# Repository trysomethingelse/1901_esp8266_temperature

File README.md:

# ESP8266_temperature
ESP8266 works as MQTT client and sends temperature to MQTT Broker. Paho client in python reads new data and saves in sql database. HTTP server with Dash reads new data when site is refreshed and shows it on graph.

## How to start?
(tested on Windows 10)
1. Flash new firmware to yours ESP (working firmware is at firmware location on GitHub)
2. Upload all files from LUA folder to your ESP and create additional file ("credentials.lua") with your wifi network infromation as given below:

`SSID = "ssid_of_your_network"`

`PASSWORD = "password_of_your_network"`
 
3. Run mosquitto broker

4. Run python script `main.py` . Script will create database file at location and name given inside script. Then received data from esp will go to database. Http server should be available at default address http://127.0.0.1:8050/

:exclamation: At first run of ESP network should be available because of time synchronization. If not esp will stuck. After first synchronization data will be saved in memory if network will be not accessible and in new connection all of it will be transmitted.

## How to change time interval of deep sleep with MQTT?

Publish to path: esp/set where message is time interval in seconds, max is about 71 min.

For example:

`mosquitto_pub -t esp/set -m 60 -h 192.168.137.1`

## Electronic schematic:

## Data presentation:

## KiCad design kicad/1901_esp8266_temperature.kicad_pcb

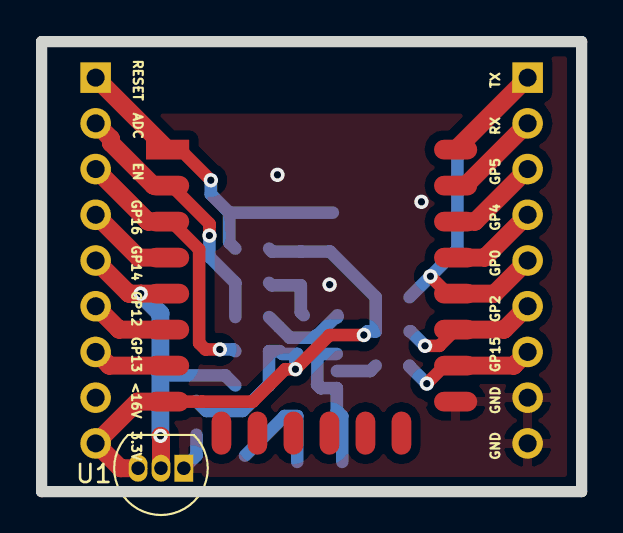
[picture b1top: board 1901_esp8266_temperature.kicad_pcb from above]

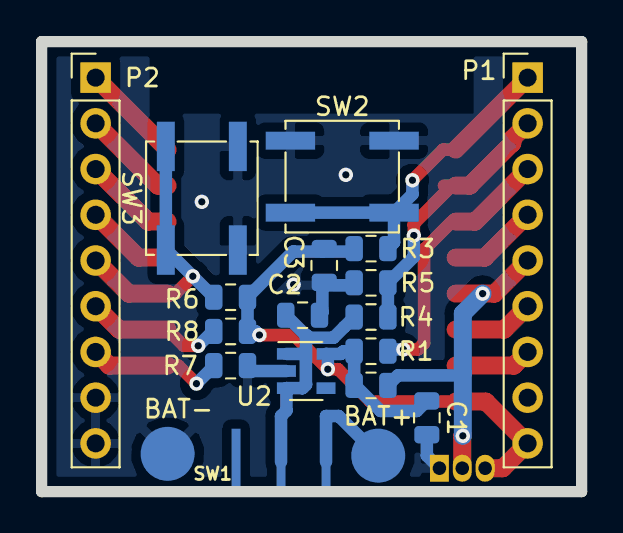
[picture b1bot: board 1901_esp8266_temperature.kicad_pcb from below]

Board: 2 copper layers, 30.0 x 25.0 mm, 21 parts (19 on the bottom side), 18 nets.

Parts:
BAT+: PAD_BAT+; Pad
BAT-: PAD_BAT-; Pad
C1: 22uF; C_0805_2012Metric
C2, C3: 1uF; C_0805_2012Metric
P1, P2: CONN_01X09; PinHeader_1x09_P2.54mm_Vertical
R1, R3, R6, R7, R8: 10KΩ; R_0805_2012Metric
R2: 4.7k; R_0805_2012Metric
R4, R5: 1MΩ; R_0805_2012Metric
SW1: pkl_SWITCH-SPDT; SW_SS12D00_SMD
SW2: SW_RESET; SW_SPST_EVPBF
SW3: SW_FLASH; SW_SPST_EVPBF
U1: DS18B20; TO-92_Inline
U2: XC6210B332MR; SOT-23-5
U3: ESP-12E

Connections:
+3V3: C1.1, C3.1, P1.9, R1.1, R2.1, R3.1, R6.1, R8.1, U1.3, U2.5, U3.8
+BATT: C2.1, R4.1, SW1.2, U2.1, U2.3
BATT_SENSE: P1.2, R4.2, R5.1, U3.2
DS_TEMP: P1.5, R2.2, U1.2, U3.5
GND: BAT-.1, C1.2, C2.2, C3.2, P2.8, P2.9, R5.2, R7.2, SW2.1, SW3.2, U1.1, U2.2, U3.15
unnamed: P1.1, R3.2, SW2.2, U3.1
unnamed: P1.3, R1.2, U3.3
unnamed: P1.4, U3.4
unnamed: P1.6, U3.6
unnamed: P1.7, U3.7
unnamed: P2.1, U3.22
unnamed: P2.2, U3.21
unnamed: P2.3, U3.20
unnamed: P2.4, U3.19
unnamed: P2.5, R6.2, SW3.1, U3.18
unnamed: P2.6, R8.2, U3.17
unnamed: P2.7, R7.1, U3.16
unnamed: BAT+.1, SW1.1

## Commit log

2019-11-14 init
2019-11-14 adding programs
2023-03-09 Create LICENSE
